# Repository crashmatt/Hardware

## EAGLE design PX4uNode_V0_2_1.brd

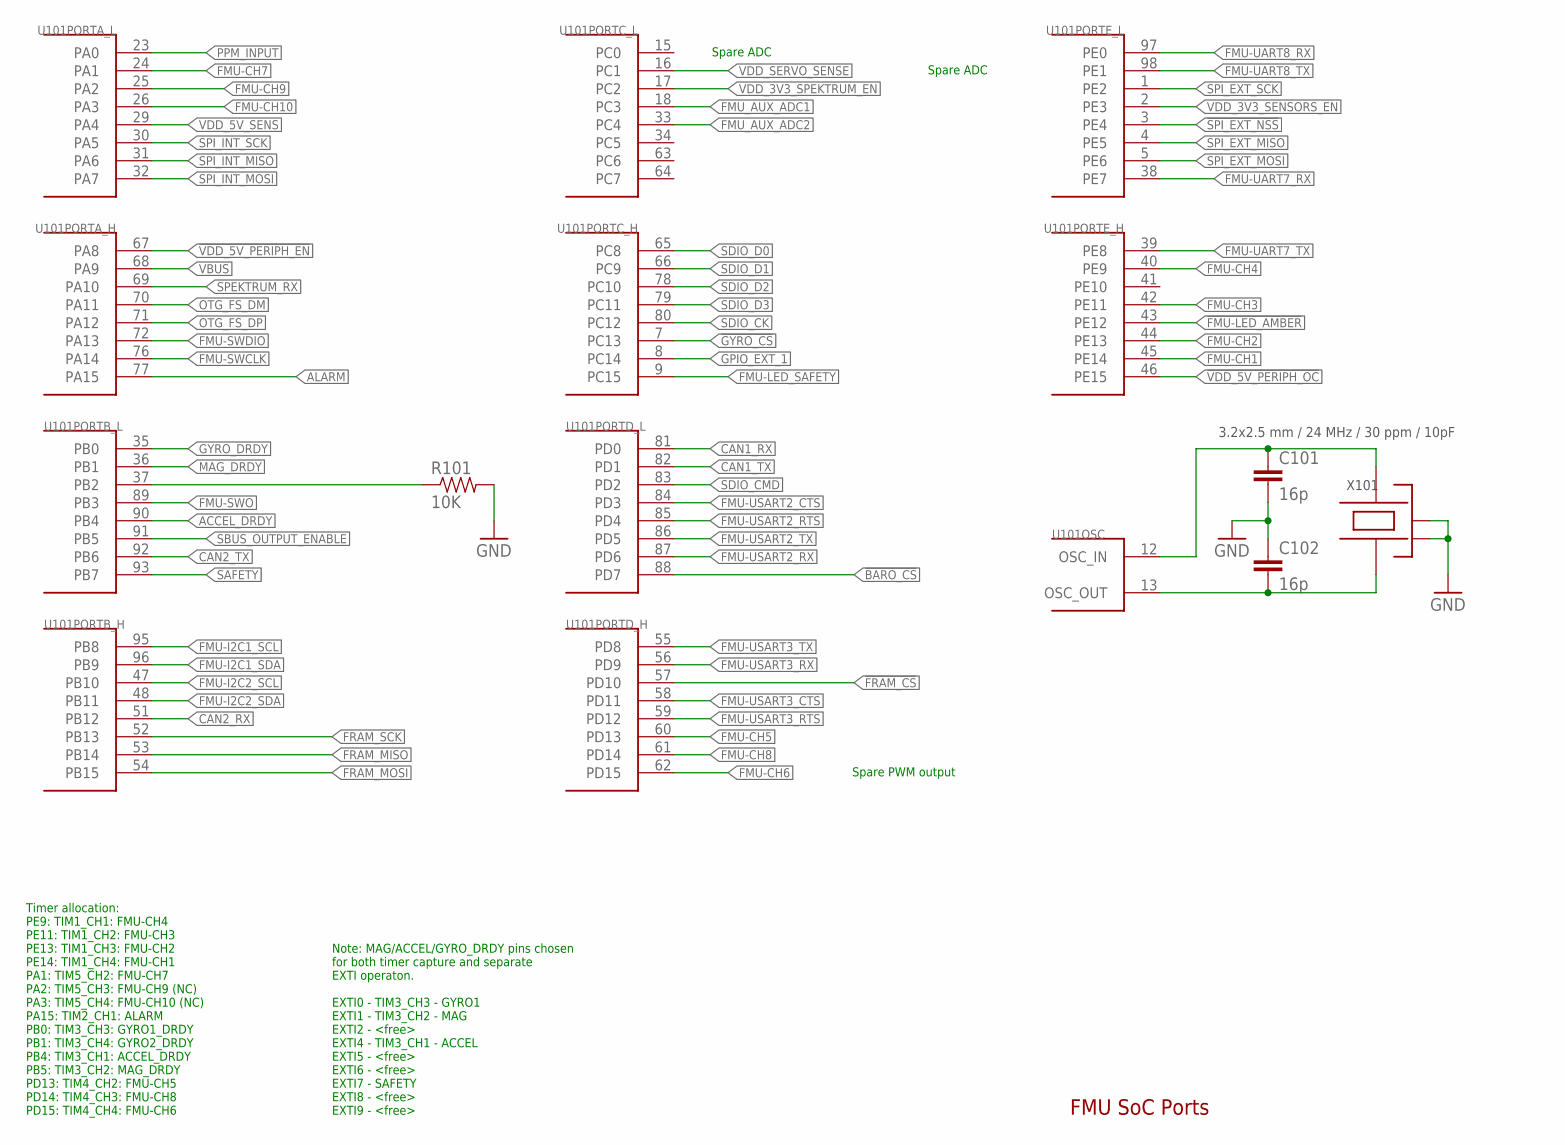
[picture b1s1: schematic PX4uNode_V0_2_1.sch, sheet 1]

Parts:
C101, C102: 16p; 0402-CAP; PARTNO C1005C0G1H160
R101: 10K; 0402-RES; PARTNO RC0402FR-0710KL
U101: STM32F4X7VX; TQFP100; PARTNO STM32F427VI
X101: 3.2x2.5 mm / 24 MHz / 30 ppm / 10pF; OSCILLATOR-3.2X2.5; PARTNO ABM8G-24.000MHZ-4Y-T3

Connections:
!BARO_CS: U101.88 (PD7)
!FMU-LED_AMBER: U101.43 (PE12); also elsewhere on the board
!FRAM_CS: U101.57 (PD10); also elsewhere on the board
!GYRO_CS: U101.7 (PC13); also elsewhere on the board
!SPI_EXT_NSS: U101.3 (PE4); also elsewhere on the board
!VDD_5V_PERIPH_EN: U101.67 (PA8); also elsewhere on the board
!VDD_5V_PERIPH_OC: U101.46 (PE15); also elsewhere on the board
ACCEL_DRDY: U101.90 (PB4); also elsewhere on the board
ALARM: U101.77 (PA15)
CAN1_RX: U101.81 (PD0); also elsewhere on the board
CAN1_TX: U101.82 (PD1); also elsewhere on the board
CAN2_RX: U101.51 (PB12); also elsewhere on the board
CAN2_TX: U101.92 (PB6); also elsewhere on the board
CLK1: C101.P$1 (1), U101.12 (OSC_IN), X101.3
CLK2: C102.P$2 (2), U101.13 (OSC_OUT), X101.1
FMU-CH1: U101.45 (PE14); also elsewhere on the board
FMU-CH2: U101.44 (PE13); also elsewhere on the board
FMU-CH3: U101.42 (PE11); also elsewhere on the board
FMU-CH4: U101.40 (PE9); also elsewhere on the board
FMU-CH5: U101.60 (PD13); also elsewhere on the board
FMU-CH6: U101.62 (PD15); also elsewhere on the board
FMU-CH7: U101.24 (PA1); also elsewhere on the board
FMU-CH8: U101.61 (PD14); also elsewhere on the board
FMU-CH9: U101.25 (PA2); also elsewhere on the board
FMU-CH10: U101.26 (PA3); also elsewhere on the board
FMU-I2C1_SCL: U101.95 (PB8); also elsewhere on the board
FMU-I2C1_SDA: U101.96 (PB9); also elsewhere on the board
FMU-I2C2_SCL: U101.47 (PB10); also elsewhere on the board
FMU-I2C2_SDA: U101.48 (PB11); also elsewhere on the board
FMU-LED_SAFETY: U101.9 (PC15); also elsewhere on the board
FMU-SWCLK: U101.76 (PA14); also elsewhere on the board
FMU-SWDIO: U101.72 (PA13); also elsewhere on the board
FMU-SWO: U101.89 (PB3); also elsewhere on the board
FMU-UART7_RX: U101.38 (PE7); also elsewhere on the board
FMU-UART7_TX: U101.39 (PE8); also elsewhere on the board
FMU-UART8_RX: U101.97 (PE0); also elsewhere on the board
FMU-UART8_TX: U101.98 (PE1); also elsewhere on the board
FMU-USART2_CTS: U101.84 (PD3); also elsewhere on the board
FMU-USART2_RTS: U101.85 (PD4); also elsewhere on the board
FMU-USART2_RX: U101.87 (PD6); also elsewhere on the board
FMU-USART2_TX: U101.86 (PD5); also elsewhere on the board
FMU-USART3_CTS: U101.58 (PD11); also elsewhere on the board
FMU-USART3_RTS: U101.59 (PD12); also elsewhere on the board
FMU-USART3_RX: U101.56 (PD9); also elsewhere on the board
FMU-USART3_TX: U101.55 (PD8); also elsewhere on the board
FMU_AUX_ADC1: U101.18 (PC3); also elsewhere on the board
FMU_AUX_ADC2: U101.33 (PC4); also elsewhere on the board
FRAM_MISO: U101.53 (PB14); also elsewhere on the board
FRAM_MOSI: U101.54 (PB15); also elsewhere on the board
FRAM_SCK: U101.52 (PB13); also elsewhere on the board
GND: C101.P$2 (2), C102.P$1 (1), R101.P$2 (2), X101.2 (NC_2), X101.4 (NC_4); also elsewhere on the board
GPIO_EXT_1: U101.8 (PC14); also elsewhere on the board
GYRO_DRDY: U101.35 (PB0); also elsewhere on the board
MAG_DRDY: U101.36 (PB1); also elsewhere on the board
OTG_FS_DM: U101.70 (PA11); also elsewhere on the board
OTG_FS_DP: U101.71 (PA12); also elsewhere on the board
PB2-BOOT1: R101.P$1 (1), U101.37 (PB2)
PPM_INPUT: U101.23 (PA0); also elsewhere on the board
SAFETY: U101.93 (PB7); also elsewhere on the board
SBUS_OUTPUT_ENABLE: U101.91 (PB5); also elsewhere on the board
SDIO_CK: U101.80 (PC12)
SDIO_CMD: U101.83 (PD2)
SDIO_D0: U101.65 (PC8)
SDIO_D1: U101.66 (PC9)
SDIO_D2: U101.78 (PC10)
SDIO_D3: U101.79 (PC11)
SPEKTRUM_RX: U101.69 (PA10); also elsewhere on the board
SPI_EXT_MISO: U101.4 (PE5); also elsewhere on the board
SPI_EXT_MOSI: U101.5 (PE6); also elsewhere on the board
SPI_EXT_SCK: U101.1 (PE2); also elsewhere on the board
SPI_INT_MISO: U101.31 (PA6); also elsewhere on the board
SPI_INT_MOSI: U101.32 (PA7); also elsewhere on the board
SPI_INT_SCK: U101.30 (PA5); also elsewhere on the board
VBUS: U101.68 (PA9); also elsewhere on the board
VDD_3V3_SENSORS_EN: U101.2 (PE3); also elsewhere on the board
VDD_3V3_SPEKTRUM_EN: U101.17 (PC2); also elsewhere on the board
VDD_5V_SENS: U101.29 (PA4); also elsewhere on the board
VDD_SERVO_SENSE: U101.16 (PC1); also elsewhere on the board

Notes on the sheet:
FMU SoC Ports
Note: MAG/ACCEL/GYRO_DRDY pins chosen for both timer capture and separate EXTI operaton. EXTI0 - TIM3_CH3 - GYRO1 EXTI1 - TIM3_CH2 - MAG EXTI2 - <free> EXTI4 - TIM3_CH1 - ACCEL EXTI5 - <free> EXTI6 - <free> EXTI7 - SAFETY EXTI8 - <free> EXTI9 - <free>
Timer allocation: PE9: TIM1_CH1: FMU-CH4 PE11: TIM1_CH2: FMU-CH3 PE13: TIM1_CH3: FMU-CH2 PE14: TIM1_CH4: FMU-CH1 PA1: TIM5_CH2: FMU-CH7 PA2: TIM5_CH3: FMU-CH9 (NC) PA3: TIM5_CH4: FMU-CH10 (NC) PA15: TIM2_CH1: ALARM PB0: TIM3_CH3: GYRO1_DRDY PB1: TIM3_CH4: GYRO2_DRDY PB4: TIM3_CH1: ACCEL_DRDY PB5: T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
Spare PWM output
Spare ADC

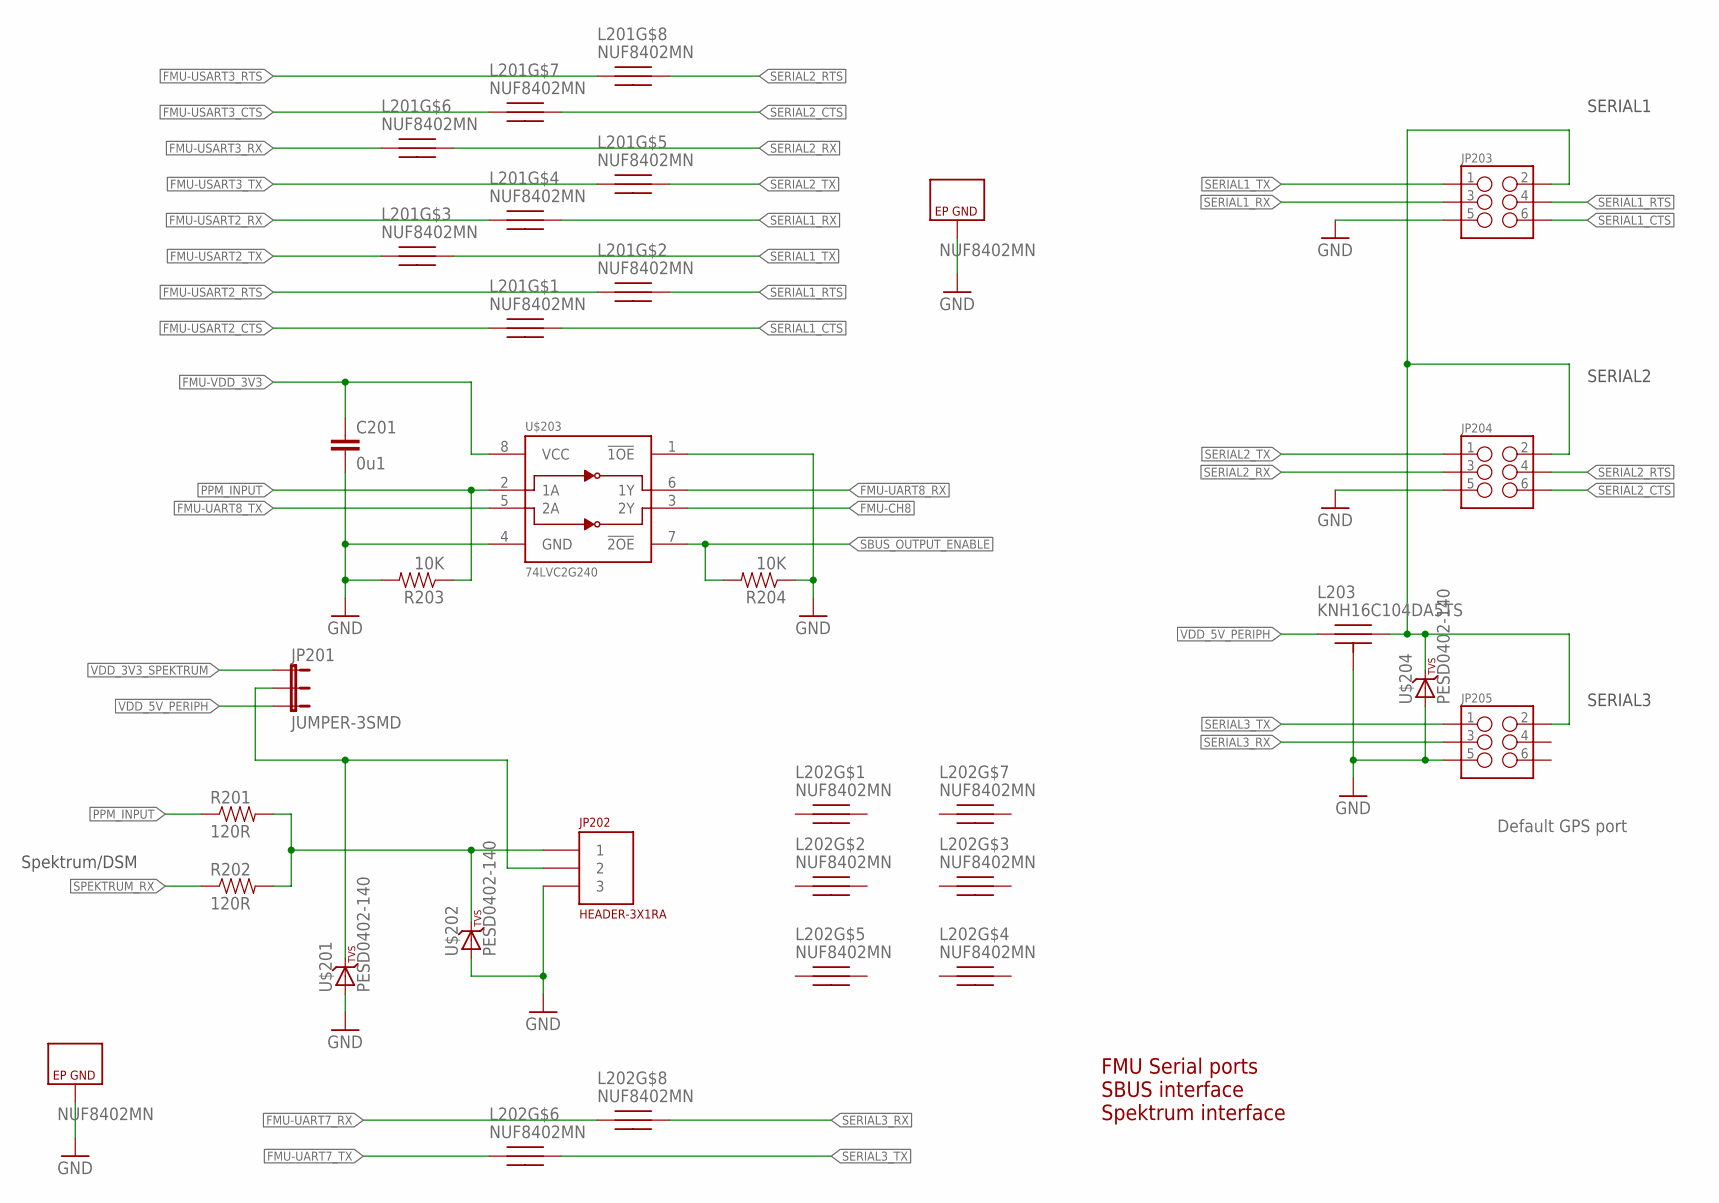
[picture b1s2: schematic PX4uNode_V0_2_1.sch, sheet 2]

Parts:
C201: 0u1; 0402-CAP; PARTNO CC0402ZRY5V7BB104
JP201: JUMPER-3SMD; SJ_3
JP202: HEADER-3X1RA; 3X1RA
JP203, JP204, JP205: M03X22X3_SILK_SM; 2X3
L201, L202: NUF8402MN; DFN16-THIN; PARTNO NUF8402MN
L203: KNH16C104DA5TS; KYOCERA-KNH16-DA; PARTNO KNH16C104DA5TS
R201, R202: 120R; 0402-RES; PARTNO RC0402FR-07120RL
R203, R204: 10K; 0402-RES; PARTNO RC0402FR-0710KL
U$201, U$202, U$204: PESD0402-140; 0402-TVS; PARTNO PESD0402-140
U$203: 74LVC2G240; VSSOP8; PARTNO 74LVC2G240

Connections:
5V_S3_FILTERED: JP203.2, JP204.2, JP205.2, L203.P$2, U$204.C
FMU-CH8: U$203.3 (2Y); also elsewhere on the board
FMU-UART7_RX: L202.P$8; also elsewhere on the board
FMU-UART7_TX: L202.P$6; also elsewhere on the board
FMU-UART8_RX: U$203.6 (1Y); also elsewhere on the board
FMU-UART8_TX: U$203.5 (2A); also elsewhere on the board
FMU-USART2_CTS: L201.P$1; also elsewhere on the board
FMU-USART2_RTS: L201.P$2; also elsewhere on the board
FMU-USART2_RX: L201.P$4; also elsewhere on the board
FMU-USART2_TX: L201.P$3; also elsewhere on the board
FMU-USART3_CTS: L201.P$7; also elsewhere on the board
FMU-USART3_RTS: L201.P$8; also elsewhere on the board
FMU-USART3_RX: L201.P$6; also elsewhere on the board
FMU-USART3_TX: L201.P$5; also elsewhere on the board
FMU-VDD_3V3: C201.P$1 (1), U$203.8 (VCC); also elsewhere on the board
GND: C201.P$2 (2), JP202.3, JP203.5, JP204.5, JP205.5, L201.P$EP (GND), L202.P$EP (GND), L203.P$3, L203.P$4, L203.P$5, R203.P$2 (2), R204.P$1 (1), U$201.A, U$202.A, U$203.1 (!1OE), U$203.4 (GND), U$204.A; also elsewhere on the board
unnamed: JP202.1, R201.P$2 (2), R202.P$2 (2), U$202.C
unnamed: JP201.2, JP202.2, U$201.C
PPM_INPUT: R201.P$1 (1), R203.P$1 (1), U$203.2 (1A); also elsewhere on the board
SBUS_OUTPUT_ENABLE: R204.P$2 (2), U$203.7 (!2OE); also elsewhere on the board
SERIAL1_CTS: JP203.6, L201.P$16
SERIAL1_RTS: JP203.4, L201.P$15
SERIAL1_RX: JP203.3, L201.P$13
SERIAL1_TX: JP203.1, L201.P$14
SERIAL2_CTS: JP204.6, L201.P$10
SERIAL2_RTS: JP204.4, L201.P$9
SERIAL2_RX: JP204.3, L201.P$11
SERIAL2_TX: JP204.1, L201.P$12
SERIAL3_RX: JP205.3, L202.P$9
SERIAL3_TX: JP205.1, L202.P$11
SPEKTRUM_RX: R202.P$1 (1); also elsewhere on the board
VDD_3V3_SPEKTRUM: JP201.1; also elsewhere on the board
VDD_5V_PERIPH: JP201.3, L203.P$1; also elsewhere on the board

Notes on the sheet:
FMU Serial ports SBUS interface Spektrum interface
SERIAL2
SERIAL1
SERIAL3
Default GPS port
Spektrum/DSM

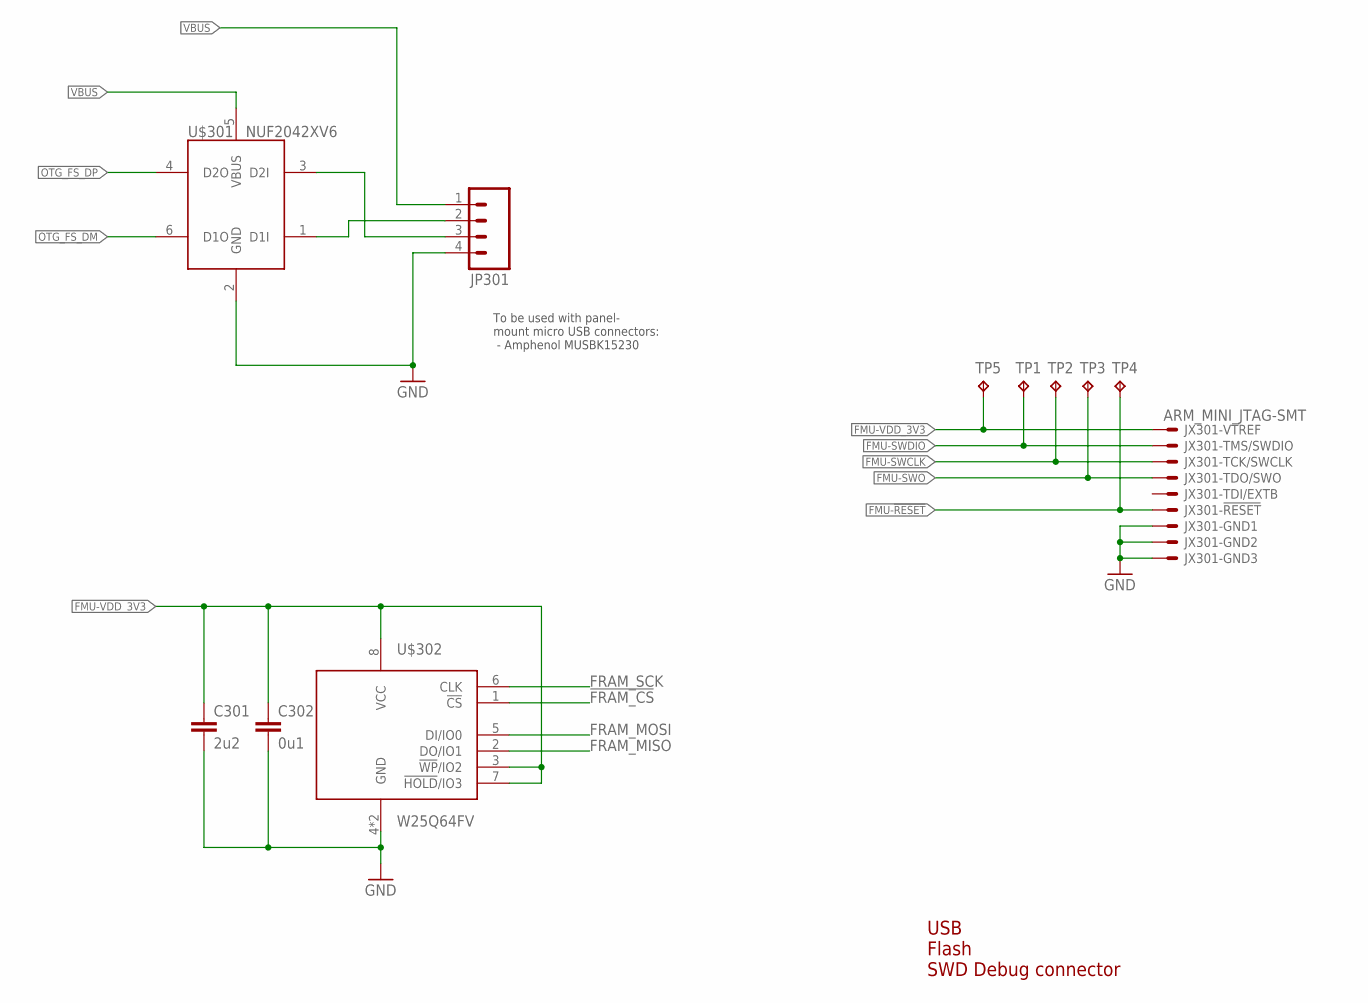
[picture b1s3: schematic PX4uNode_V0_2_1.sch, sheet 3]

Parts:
C301: 2u2; 0603-CAP; PARTNO C1608Y5V1C225Z
C302: 0u1; 0402-CAP; PARTNO CC0402ZRY5V7BB104
JP301: M04PTH; 1X04
JX301: ARM_MINI_JTAG-SMT; FTSH-105-01-XXX-DV-K; PARTNO M50-3900542
TP1, TP2, TP3, TP4, TP5: TPTP20R; TP20R
U$301: NUF2042XV6; SOT563-6; PARTNO NUF2042XV6
U$302: W25Q64FV; WSON-8-5X6; PARTNO W25Q64FVZP

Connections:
!FRAM_CS: U$302.1 (!CS); also elsewhere on the board
FMU-!RESET: JX301.10, TP4.TP; also elsewhere on the board
FMU-SWCLK: JX301.4, TP2.TP; also elsewhere on the board
FMU-SWDIO: JX301.2, TP1.TP; also elsewhere on the board
FMU-SWO: JX301.6, TP3.TP; also elsewhere on the board
FMU-VDD_3V3: C301.P$1 (1), C302.P$1 (1), JX301.1, TP5.TP, U$302.3 (!WP!/IO2), U$302.7 (!HOLD!/IO3), U$302.8 (VCC); also elsewhere on the board
FRAM_MISO: U$302.2 (DO/IO1); also elsewhere on the board
FRAM_MOSI: U$302.5 (DI/IO0); also elsewhere on the board
FRAM_SCK: U$302.6 (CLK); also elsewhere on the board
GND: C301.P$2 (2), C302.P$2 (2), JP301.4, JX301.3, JX301.5, JX301.9, U$301.2 (GND), U$302.4 (GND), U$302.PAD (GND); also elsewhere on the board
OTG_FS_DM: U$301.6 (D1O); also elsewhere on the board
OTG_FS_DP: U$301.4 (D2O); also elsewhere on the board
UDB_DP: JP301.3, U$301.3 (D2I)
USB_DM: JP301.2, U$301.1 (D1I)
VBUS: JP301.1, U$301.5 (VBUS); also elsewhere on the board

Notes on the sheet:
USB Flash SWD Debug connector
To be used with panel- mount micro USB connectors: - Amphenol MUSBK15230

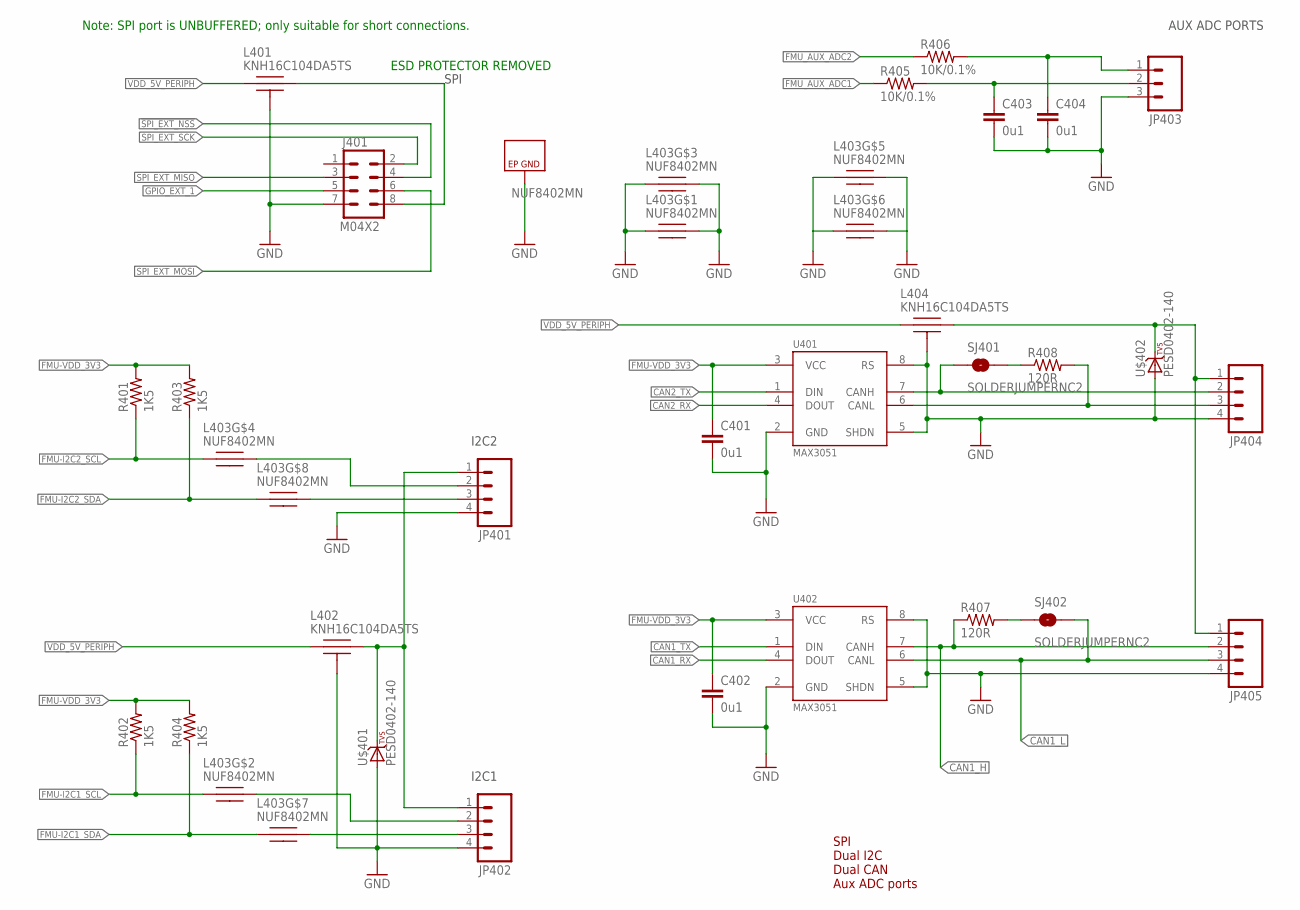
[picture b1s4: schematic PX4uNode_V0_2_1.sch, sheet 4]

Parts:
C401, C402, C403, C404: 0u1; 0402-CAP; PARTNO CC0402ZRY5V7BB104
J401: M04X2; 2X4
JP401, JP402, JP404, JP405: M04PTH; 1X04
JP403: M03PTH; 1X03; PARTNO EXCLUDE
L401, L402, L404: KNH16C104DA5TS; KYOCERA-KNH16-DA; PARTNO KNH16C104DA5TS
L403: NUF8402MN; DFN16-THIN; PARTNO NUF8402MN
R401, R402, R403, R404: 1K5; 0402-RES; PARTNO RC0402FR-071K5L
R405, R406: 10K/0.1%; 0402-RES; PARTNO ERA-2AEB103X
R407, R408: 120R; 0402-RES; PARTNO RC0402FR-07120RL
SJ401, SJ402: SOLDERJUMPERNC2; SJ_2S-NOTRACE
U401, U402: MAX3051; SOT23-8; PARTNO MAX3051EKA
U$401, U$402: PESD0402-140; 0402-TVS; PARTNO PESD0402-140

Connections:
!SPI_EXT_NSS: J401.4; also elsewhere on the board
CAN1_H: JP405.2, R407.P$1 (1), U402.7 (CANH)
CAN1_L: JP405.3, SJ402.2, U402.6 (CANL)
CAN1_RX: U402.4 (DOUT); also elsewhere on the board
CAN1_TX: U402.1 (DIN); also elsewhere on the board
CAN2_H: JP404.2, SJ401.1, U401.7 (CANH)
CAN2_L: JP404.3, R408.P$2 (2), U401.6 (CANL)
CAN2_RX: U401.4 (DOUT); also elsewhere on the board
CAN2_TX: U401.1 (DIN); also elsewhere on the board
FMU-I2C1_SCL: L403.P$2, R402.P$1 (1); also elsewhere on the board
FMU-I2C1_SDA: L403.P$7, R404.P$1 (1); also elsewhere on the board
FMU-I2C2_SCL: L403.P$4, R401.P$1 (1); also elsewhere on the board
FMU-I2C2_SDA: L403.P$8, R403.P$1 (1); also elsewhere on the board
FMU-VDD_3V3: C401.P$1 (1), C402.P$1 (1), R401.P$2 (2), R402.P$2 (2), R403.P$2 (2), R404.P$2 (2), U401.3 (VCC), U402.3 (VCC); also elsewhere on the board
FMU_AUX_ADC1: R405.P$1 (1); also elsewhere on the board
FMU_AUX_ADC1_PROT: C403.P$1 (1), JP403.2, R405.P$2 (2)
FMU_AUX_ADC2: R406.P$1 (1); also elsewhere on the board
FMU_AUX_ADC2_PROT: C404.P$1 (1), JP403.1, R406.P$2 (2)
GND: C401.P$2 (2), C402.P$2 (2), C403.P$2 (2), C404.P$2 (2), J401.7, JP401.4, JP402.4, JP403.3, JP404.4, JP405.4, L401.P$3, L401.P$4, L401.P$5, L402.P$3, L402.P$4, L402.P$5, L403.P$1, L403.P$3, L403.P$5, L403.P$6, L403.P$11, L403.P$12, L403.P$14, L403.P$16, L403.P$EP (GND), L404.P$3, L404.P$4, L404.P$5, U401.2 (GND), U401.5 (SHDN), U401.8 (RS), U402.2 (GND), U402.5 (SHDN), U402.8 (RS), U$401.A, U$402.A; also elsewhere on the board
GPIO_EXT_1: J401.5; also elsewhere on the board
IC2_VDD_5V: JP401.1, JP402.1, L402.P$2, U$401.C
unnamed: JP401.2, L403.P$13
unnamed: JP401.3, L403.P$9
unnamed: R408.P$1 (1), SJ401.2
unnamed: R407.P$2 (2), SJ402.1
unnamed: JP404.1, JP405.1, L404.P$2, U$402.C
unnamed: JP402.2, L403.P$15
unnamed: JP402.3, L403.P$10
unnamed: J401.8, L401.P$2
SPI_EXT_MISO: J401.3; also elsewhere on the board
SPI_EXT_MOSI: J401.6; also elsewhere on the board
SPI_EXT_SCK: J401.2; also elsewhere on the board
VDD_5V_PERIPH: L401.P$1, L402.P$1, L404.P$1; also elsewhere on the board

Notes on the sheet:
SPI
I2C2
AUX ADC PORTS
SPI Dual I2C Dual CAN Aux ADC ports
Note: SPI port is UNBUFFERED; only suitable for short connections.
I2C1
ESD PROTECTOR REMOVED

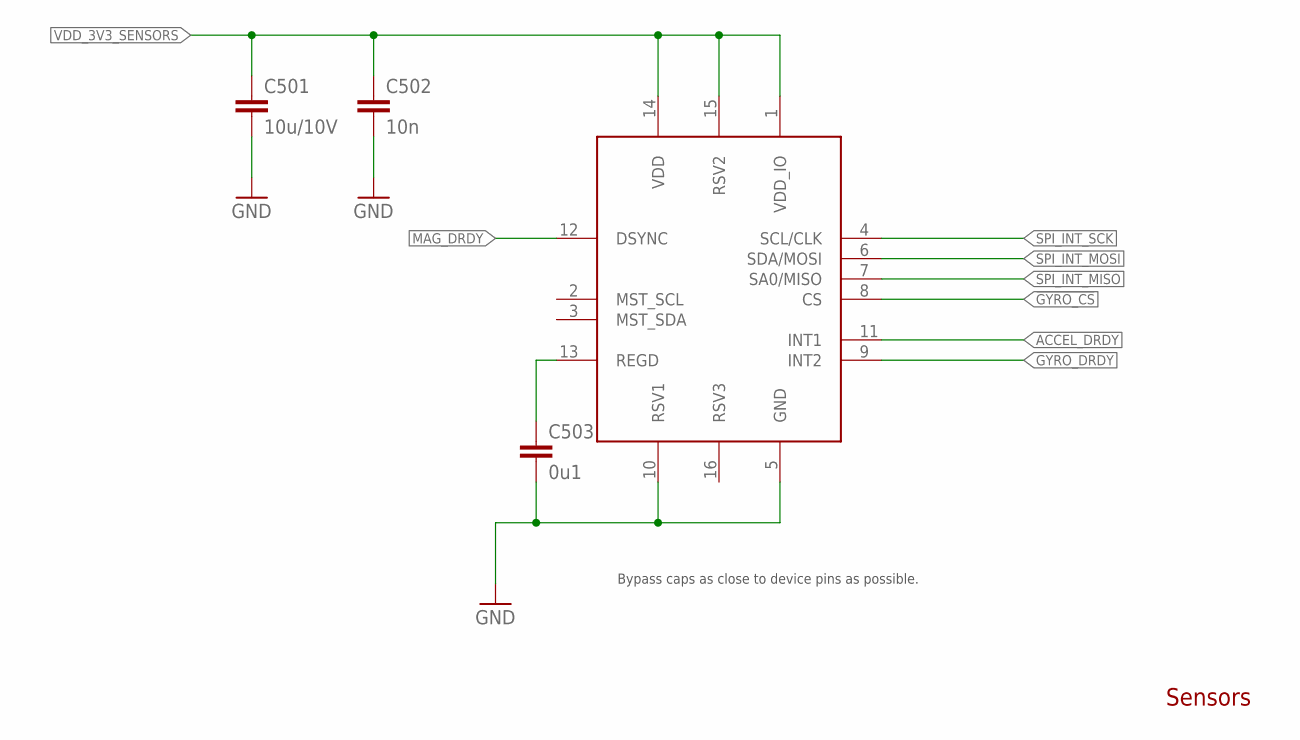
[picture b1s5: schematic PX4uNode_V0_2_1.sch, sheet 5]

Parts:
C501: 10u/10V; 0805-CAP; PARTNO CC0805ZKY5V6BB106
C502: 10n; 0402-CAP; PARTNO CC0402KRX7R7BB103
C503: 0u1; 0402-CAP; PARTNO CC0402ZRY5V7BB104
U$501: MAX21100; 16LGA-3X3; PARTNO MAX21100+

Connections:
!GYRO_CS: U$501.8 (CS); also elsewhere on the board
ACCEL_DRDY: U$501.11 (INT1); also elsewhere on the board
GND: C501.P$2 (2), C502.P$2 (2), C503.P$2 (2), U$501.5 (GND), U$501.10 (RSV1); also elsewhere on the board
GYRO_DRDY: U$501.9 (INT2); also elsewhere on the board
MAG_DRDY: U$501.12 (DSYNC); also elsewhere on the board
REGD: C503.P$1 (1), U$501.13 (REGD)
SPI_INT_MISO: U$501.7 (SA0/MISO); also elsewhere on the board
SPI_INT_MOSI: U$501.6 (SDA/MOSI); also elsewhere on the board
SPI_INT_SCK: U$501.4 (SCL/CLK); also elsewhere on the board
VDD_3V3_SENSORS: C501.P$1 (1), C502.P$1 (1), U$501.1 (VDD_IO), U$501.14 (VDD), U$501.15 (RSV2); also elsewhere on the board

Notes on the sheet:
Sensors
Bypass caps as close to device pins as possible.

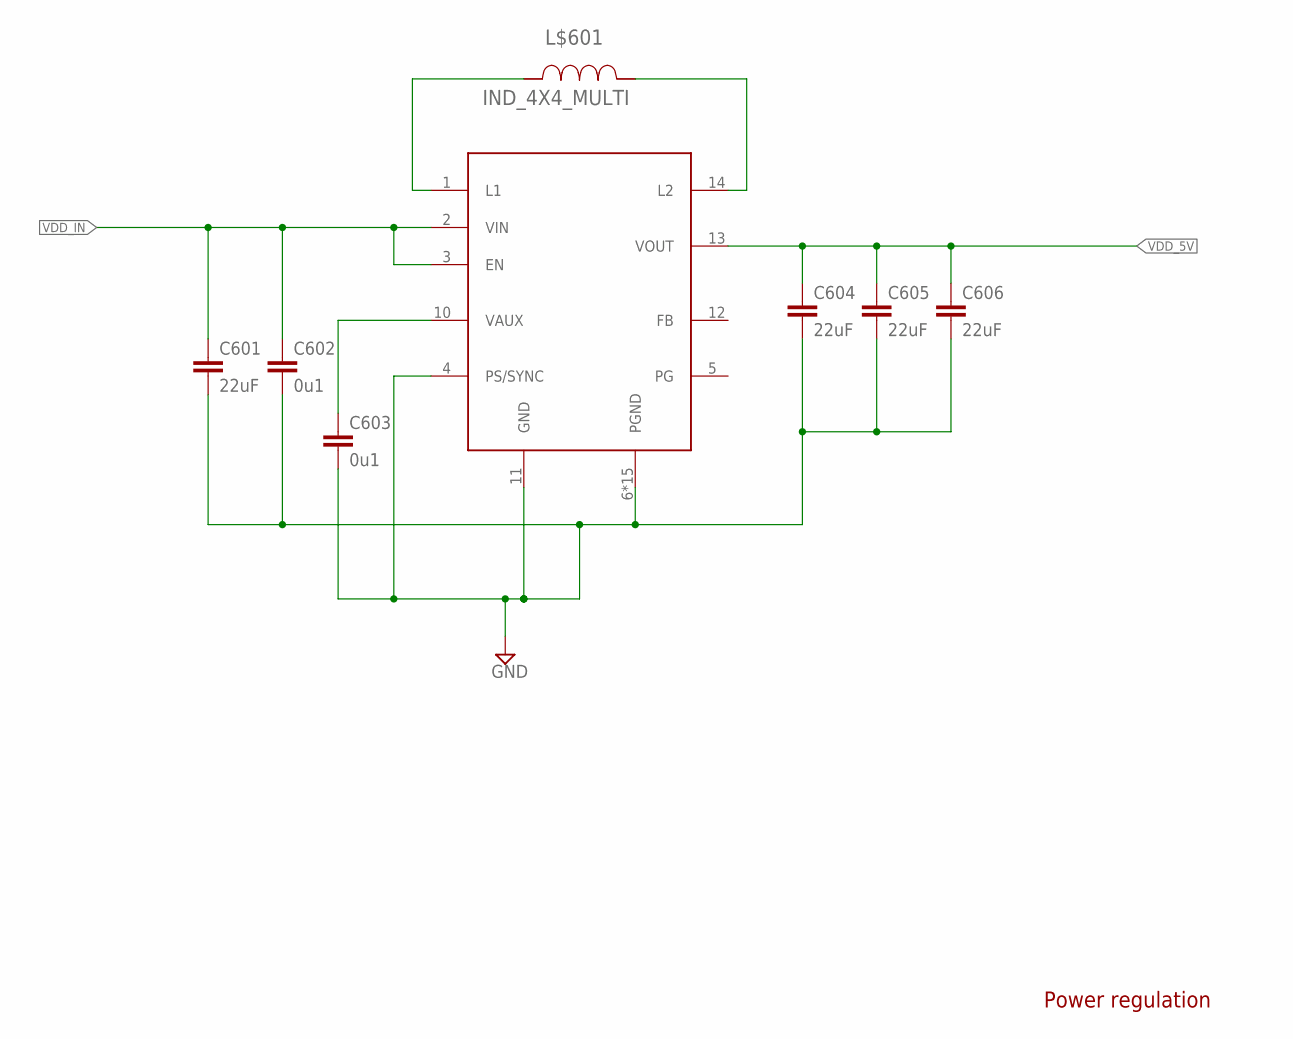
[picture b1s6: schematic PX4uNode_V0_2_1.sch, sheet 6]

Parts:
C601, C604, C605, C606: 22uF; 1210; PARTNO C3225X7R1C226M250AC
C602, C603: 0u1; 0402-CAP; PARTNO CC0402ZRY5V7BB104
L$601: IND_4X4_MULTI; PARTNO XFL4020-222MEB
U$601: TPS6303X; PWSON10; PARTNO TPS63061DSCT

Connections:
GND: C601.2, C602.P$2 (2), C603.P$2 (2), C604.2, C605.2, C606.2, U$601.4 (PS/SYNC), U$601.6 (PGND), U$601.7 (PGND), U$601.8 (PGND), U$601.9 (PGND), U$601.11 (GND), U$601.15 (PGND), U$601.16 (PGND), U$601.17 (PGND), U$601.18 (PGND), U$601.19 (PGND), U$601.20 (PGND), U$601.21 (PGND), U$601.22 (PGND), U$601.23 (PGND), U$601.EP (PGND), U$601.EP1 (PGND); also elsewhere on the board
unnamed: L$601.1, U$601.14 (L2)
unnamed: L$601.2, U$601.1 (L1)
unnamed: C603.P$1 (1), U$601.10 (VAUX)
VDD_5V: C604.1, C605.1, C606.1, U$601.13 (VOUT); also elsewhere on the board
VDD_IN: C601.1, C602.P$1 (1), U$601.2 (VIN), U$601.3 (EN); also elsewhere on the board

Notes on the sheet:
Power regulation

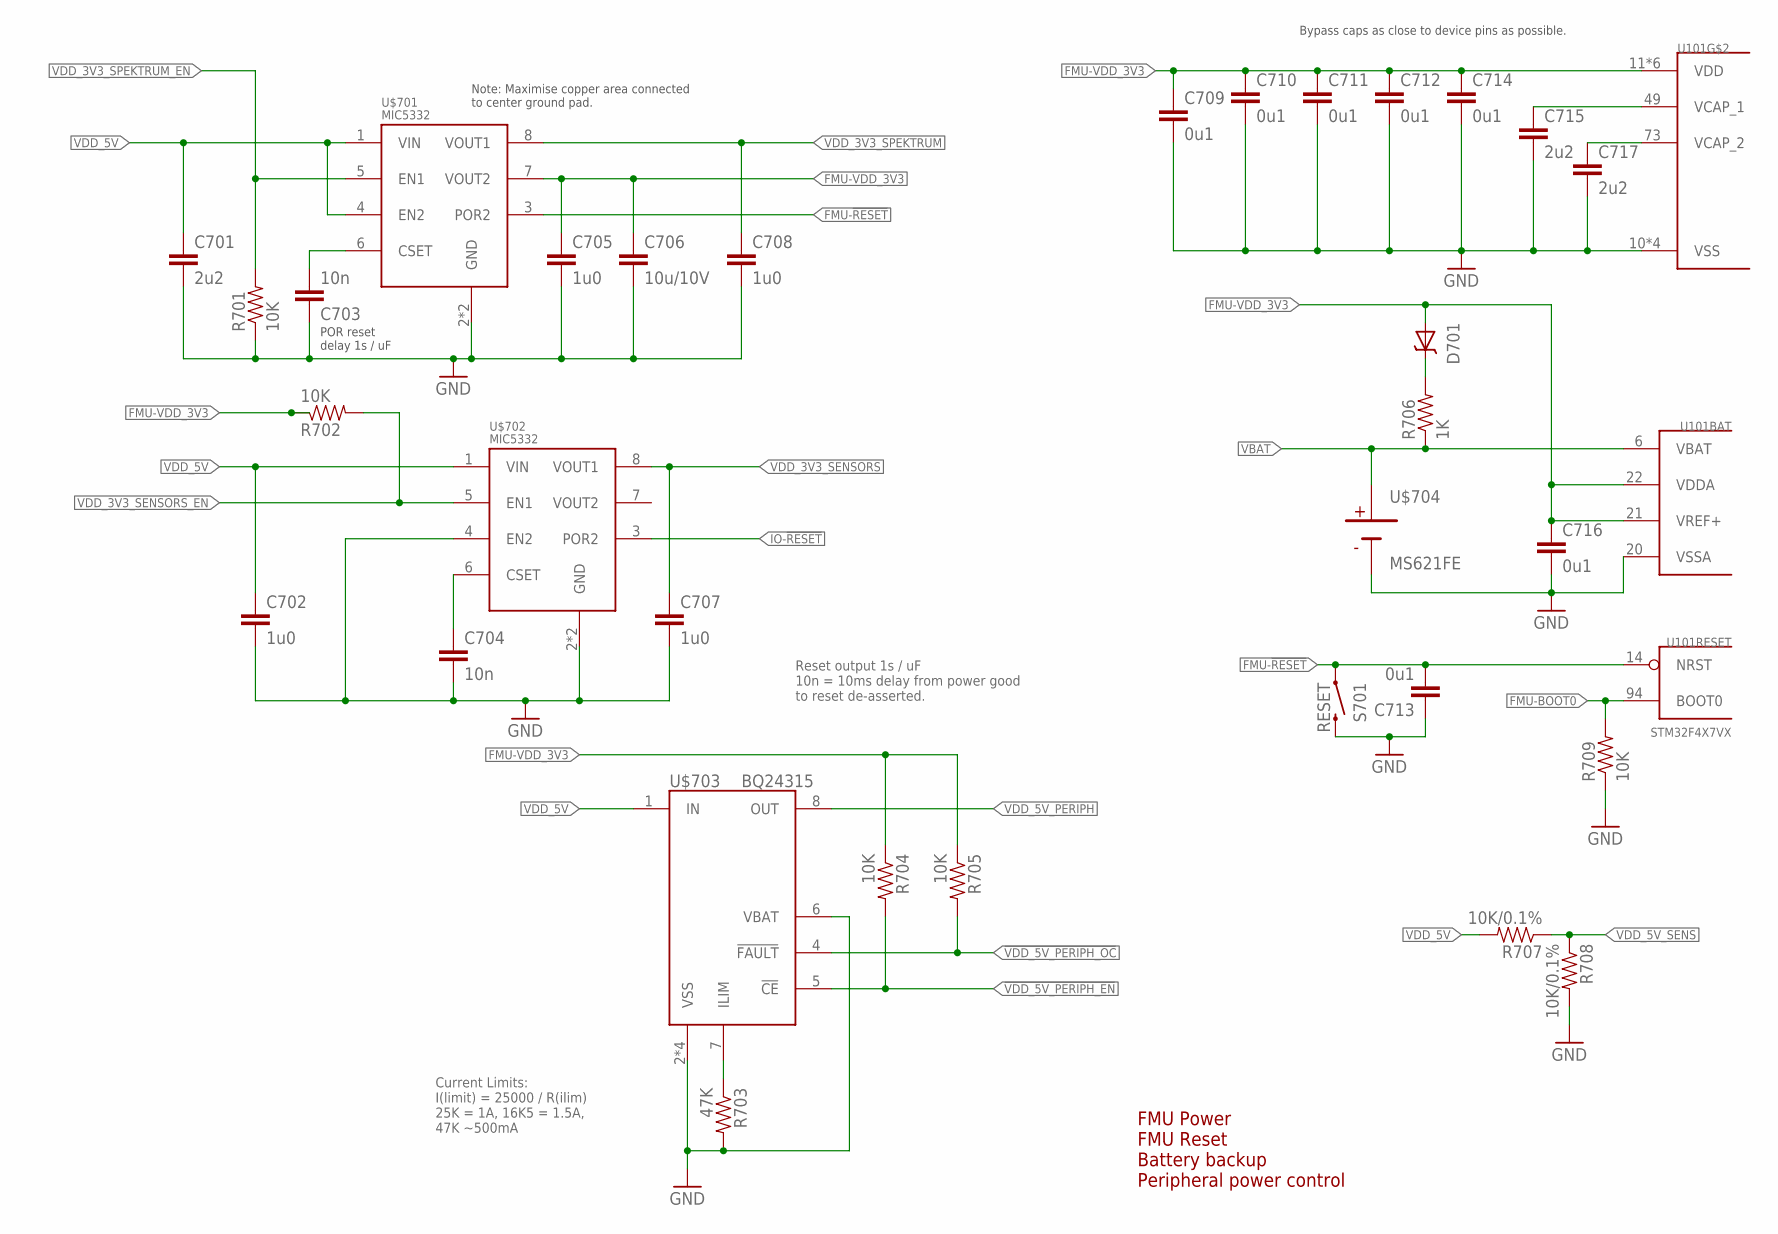
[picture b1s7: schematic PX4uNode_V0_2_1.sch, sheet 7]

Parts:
C701, C715, C717: 2u2; 0603-CAP; PARTNO C1608Y5V1C225Z
C702, C705, C707, C708: 1u0; 0603-CAP; PARTNO CC0603ZRY5V7BB105
C703, C704: 10n; 0402-CAP; PARTNO CC0402KRX7R7BB103
C706: 10u/10V; 0805-CAP; PARTNO CC0805ZKY5V6BB106
C709, C710, C711, C712, C713, C714, C716: 0u1; 0402-CAP; PARTNO CC0402ZRY5V7BB104
D701: DIODE-SCHOTTKY; SOD-523; PARTNO MBRA140
R701, R702, R704, R705, R709: 10K; 0402-RES; PARTNO RC0402FR-0710KL
R703: 47K; 0402-RES; PARTNO RMCF0402FT47K
R706: 1K; 0402-RES; PARTNO RC0402FR-071KL
R707, R708: 10K/0.1%; 0402-RES; PARTNO ERA-2AEB103X
S701: RESET; EVQP7J01K; PARTNO EVQP7J01K
U101: STM32F4X7VX; TQFP100; PARTNO STM32F427VI
U$701, U$702: MIC5332; MLF-8-EPAD; PARTNO MIC5332-SSYMT
U$703: BQ24315; QFN8-DSG; PARTNO BQ24315DSGR
U$704: MS621FE

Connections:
!VDD_5V_PERIPH_EN: R704.P$2 (2), U$703.5 (!CE); also elsewhere on the board
!VDD_5V_PERIPH_OC: R705.P$2 (2), U$703.4 (!FAULT); also elsewhere on the board
FMU-!RESET: C713.P$2 (2), S701.A1 (1), U101.14 (NRST), U$701.3 (POR2); also elsewhere on the board
FMU-BOOT0: R709.P$2 (2), U101.94 (BOOT0); also elsewhere on the board
FMU-VDD_3V3: C705.P$1 (1), C706.P$1 (1), C709.P$1 (1), C710.P$1 (1), C711.P$1 (1), C712.P$1 (1), C714.P$1 (1), C716.P$1 (1), D701.A, R702.P$1 (1), R704.P$1 (1), R705.P$1 (1), U101.11 (VDD), U101.19 (VDD), U101.21 (VREF+), U101.22 (VDDA), U101.28 (VDD), U101.50 (VDD), U101.75 (VDD), U101.100 (VDD), U$701.7 (VOUT2); also elsewhere on the board
GND: C701.P$2 (2), C702.P$2 (2), C703.P$1 (1), C704.P$2 (2), C705.P$2 (2), C706.P$2 (2), C707.P$2 (2), C708.P$2 (2), C709.P$2 (2), C710.P$2 (2), C711.P$2 (2), C712.P$2 (2), C713.P$1 (1), C714.P$2 (2), C715.P$2 (2), C716.P$2 (2), C717.P$2 (2), R701.P$1 (1), R703.P$2 (2), R708.P$2 (2), R709.P$1 (1), S701.B3 (2), U101.10 (VSS), U101.20 (VSSA), U101.27 (VSS), U101.74 (VSS), U101.99 (VSS), U$701.2 (GND), U$701.GND, U$702.2 (GND), U$702.4 (EN2), U$702.GND, U$703.2 (VSS), U$703.6 (VBAT), U$703.GND (VSS), U$703.P$2 (VSS), U$703.P$3 (VSS), U$704.2 (NEG); also elsewhere on the board
IO-!RESET: U$702.3 (POR2)
unnamed: D701.C, R706.P$2 (2)
unnamed: C703.P$2 (2), U$701.6 (CSET)
unnamed: R703.P$1 (1), U$703.7 (ILIM)
unnamed: C704.P$1 (1), U$702.6 (CSET)
VBAT: R706.P$1 (1), U101.6 (VBAT), U$704.1 (POS)
VCAP_1: C715.P$1 (1), U101.49 (VCAP_1)
VCAP_2: C717.P$1 (1), U101.73 (VCAP_2)
VDD_3V3_SENSORS: C707.P$1 (1), U$702.8 (VOUT1); also elsewhere on the board
VDD_3V3_SENSORS_EN: R702.P$2 (2), U$702.5 (EN1); also elsewhere on the board
VDD_3V3_SPEKTRUM: C708.P$1 (1), U$701.8 (VOUT1); also elsewhere on the board
VDD_3V3_SPEKTRUM_EN: R701.P$2 (2), U$701.5 (EN1); also elsewhere on the board
VDD_5V: C701.P$1 (1), C702.P$1 (1), R707.P$2 (2), U$701.1 (VIN), U$701.4 (EN2), U$702.1 (VIN), U$703.1 (IN); also elsewhere on the board
VDD_5V_PERIPH: U$703.8 (OUT); also elsewhere on the board
VDD_5V_SENS: R707.P$1 (1), R708.P$1 (1); also elsewhere on the board

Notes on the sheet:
FMU Power FMU Reset Battery backup Peripheral power control
Bypass caps as close to device pins as possible.
Note: Maximise copper area connected to center ground pad.
POR reset delay 1s / uF
Current Limits: I(limit) = 25000 / R(ilim) 25K = 1A, 16K5 = 1.5A, 47K ~500mA
Reset output 1s / uF 10n = 10ms delay from power good to reset de-asserted.

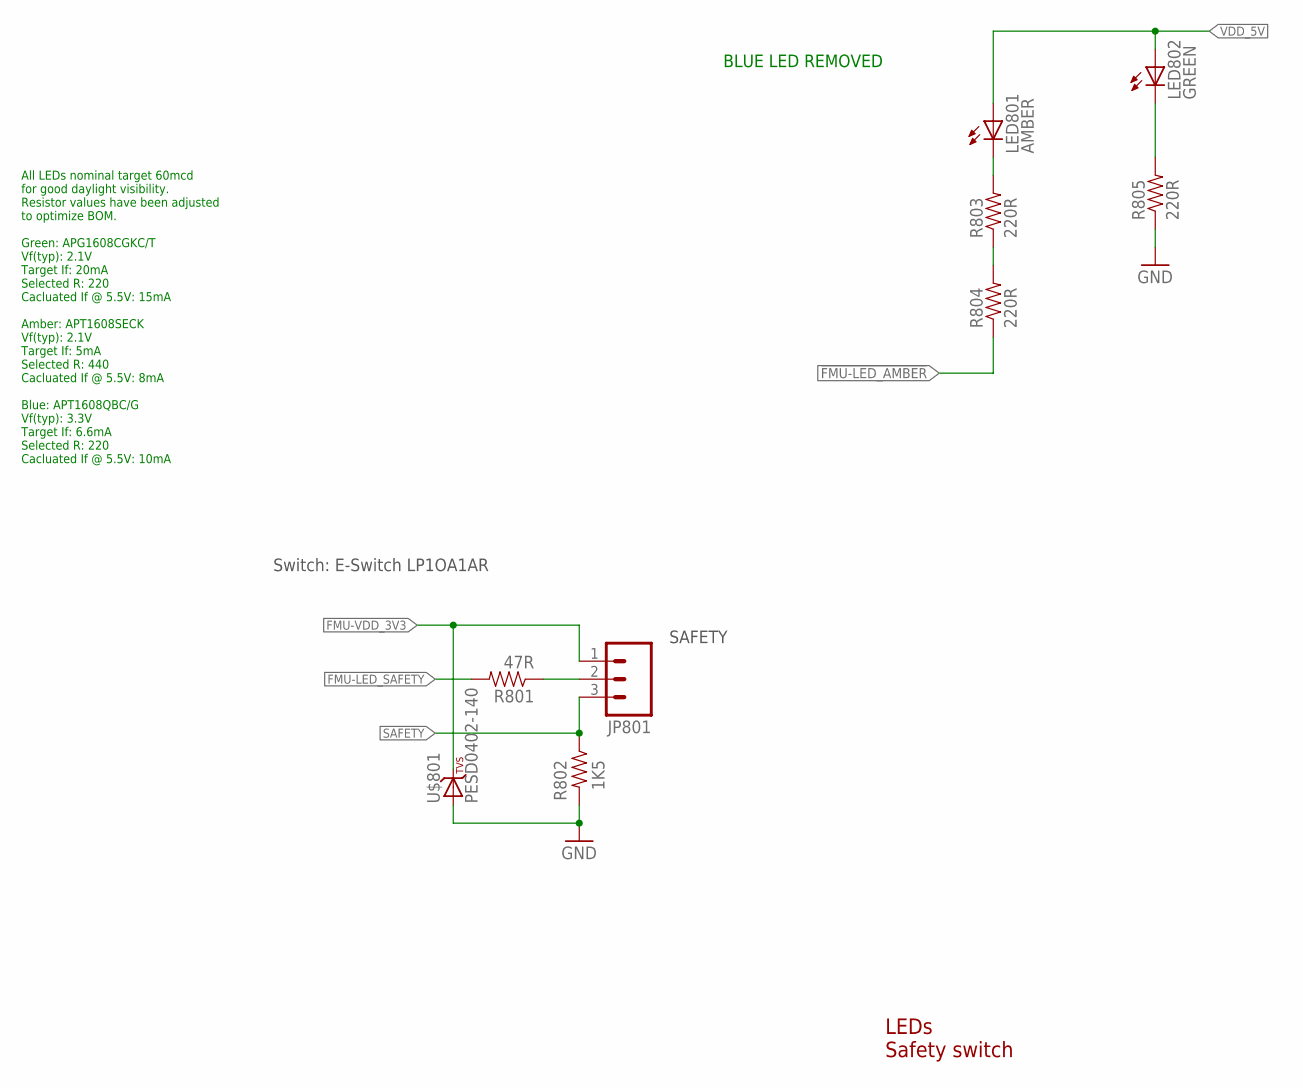
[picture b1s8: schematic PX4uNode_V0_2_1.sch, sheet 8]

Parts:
JP801: M03PTH; 1X03
LED801: AMBER; 0603-LED; PARTNO APTD1608SECK
LED802: GREEN; 0603-LED; PARTNO APTD1608CGCK
R801: 47R; 0402-RES; PARTNO RC0402JR-0747RL
R802: 1K5; 0402-RES; PARTNO RC0402FR-071K5L
R803, R804, R805: 220R; 0402-RES; PARTNO RC0402FR-07220RL
U$801: PESD0402-140; 0402-TVS; PARTNO PESD0402-140

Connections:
!FMU-LED_AMBER: R804.P$1 (1); also elsewhere on the board
FMU-LED_SAFETY: R801.P$2 (2); also elsewhere on the board
FMU-VDD_3V3: JP801.1, U$801.C; also elsewhere on the board
GND: R802.P$2 (2), R805.P$1 (1), U$801.A; also elsewhere on the board
unnamed: LED802.C, R805.P$2 (2)
unnamed: R803.P$1 (1), R804.P$2 (2)
unnamed: LED801.C, R803.P$2 (2)
unnamed: JP801.2, R801.P$1 (1)
SAFETY: JP801.3, R802.P$1 (1); also elsewhere on the board
VDD_5V: LED801.A, LED802.A; also elsewhere on the board

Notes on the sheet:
LEDs Safety switch
Switch: E-Switch LP1OA1AR
SAFETY
All LEDs nominal target 60mcd for good daylight visibility. Resistor values have been adjusted to optimize BOM. Green: APG1608CGKC/T Vf(typ): 2.1V Target If: 20mA Selected R: 220 Cacluated If @ 5.5V: 15mA Amber: APT1608SECK Vf(typ): 2.1V Target If: 5mA Selected R: 440 Cacluated If @ 5.5V: 8mA Blue: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
BLUE LED REMOVED

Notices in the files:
PX4FMUlite_V0_2.brd:
(c) 2013 mjs/lm/jo
parts and their libraries:
SparkFun-Sensors: Licensing: CC v3.0 Share-Alike You are welcome to use this library for commercial purposes.
